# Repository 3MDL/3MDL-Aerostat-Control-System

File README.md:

# Aerostat Control System #
Remote control system of Tetracam RGB+3 Multispectral camera

## Funcions currently implemented ##
- GPS parsing
- Timer based picture taking with settings via EEPROM
- General control over power of attached devices
- RGB+3 diagnostic mode auto-exit

## Functions needed to be implemented ##
- Low battery cuttoff
- Power modes?
- GPS power control on timer like camera

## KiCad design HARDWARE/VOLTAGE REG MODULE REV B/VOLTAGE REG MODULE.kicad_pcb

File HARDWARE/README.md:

# Hardware Docs #

## Load Switch Modules ##
- Utilize the Fairchild FPF2701MX load switch
- Include current shunt resistor and current set resistor

## Voltage Regulator Modules ##
- Stability issues on REV A
- Stability issues on REV B
- Currently using Recom R-78 Module

## Main Board REV C ##
- Redesign that ditches the Pi and instead only uses the ATMega328P
- Uses new Recom R-78 buck regulator module

## Main Board REV D ##
- Fixes numerous pinout issues with REV C
- Passive components moved to bottom side to aid layout
- New connectors are used that utilize side entry to compact the system further

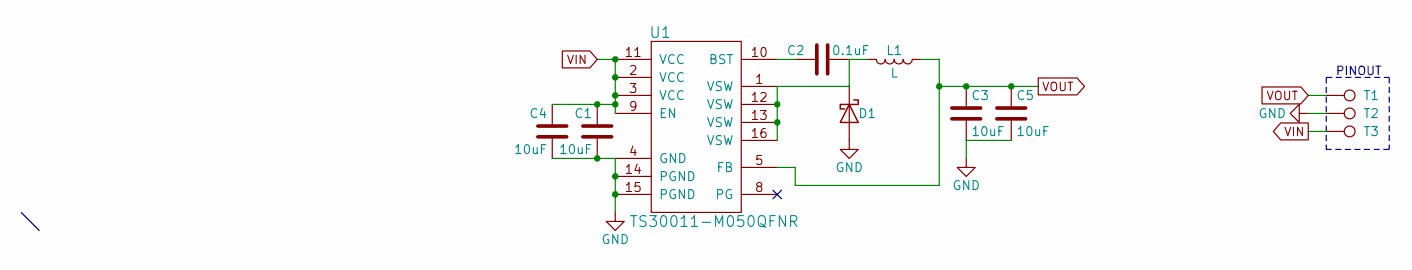
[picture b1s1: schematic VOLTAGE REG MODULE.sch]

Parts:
C1, C3, C4, C5: 10uF; C_0805
C2: 0.1uF; C_0603
D1: D_Schottky; SOD-123
L1: L; C_1210
T1, T2, T3: TEST_1P; CPAD
U1: TS30011-M050QFNR; QFN-16-1EP_3x3mm_Pitch0.5mm

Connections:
GND: C1.2, C3.2, C4.2, C5.2, D1.2 (A), T2.1, U1.4 (GND), U1.14 (PGND), U1.15 (PGND), U1.17
unnamed: C2.1, D1.1 (K), L1.2, U1.1 (VSW), U1.12 (VSW), U1.13 (VSW), U1.16 (VSW)
unnamed: C2.2, U1.10 (BST)
VIN: C1.1, C4.1, T3.1, U1.2 (VCC), U1.3 (VCC), U1.9 (EN), U1.11 (VCC)
VOUT: C3.1, C5.1, L1.1, T1.1, U1.5 (FB)

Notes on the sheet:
PINOUT

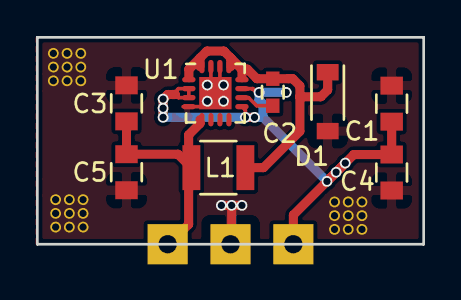
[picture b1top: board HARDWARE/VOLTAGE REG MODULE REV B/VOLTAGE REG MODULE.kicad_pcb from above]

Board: 2 copper layers, 21.5 x 11.5 mm, 11 parts (0 on the bottom side), 5 nets.

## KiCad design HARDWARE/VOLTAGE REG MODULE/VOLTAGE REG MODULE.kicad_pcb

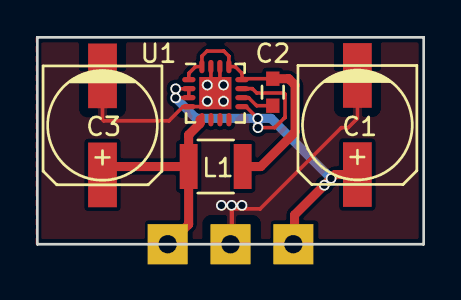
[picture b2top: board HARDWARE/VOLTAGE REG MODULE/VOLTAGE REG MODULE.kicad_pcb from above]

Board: 2 copper layers, 21.5 x 11.5 mm, 8 parts (0 on the bottom side), 5 nets.

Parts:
C1, C3: 10uF; c_elec_6.3x5.8
C2: 0.1uF; C_0603
L1: 470uH; C_1210
T1, T2, T3: TEST_1P; CPAD
U1: TS30011-M050QFNR; QFN-16-1EP_3x3mm_Pitch0.5mm

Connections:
GND: C1.2, C3.2, T3.1, U1.4, U1.14, U1.15, U1.17
unnamed: C2.1, L1.1, U1.1, U1.12, U1.13, U1.16
unnamed: C2.2, U1.10
VIN: C1.1, T1.1, U1.2, U1.3, U1.9, U1.11
VOUT: C3.1, L1.2, T2.1, U1.5

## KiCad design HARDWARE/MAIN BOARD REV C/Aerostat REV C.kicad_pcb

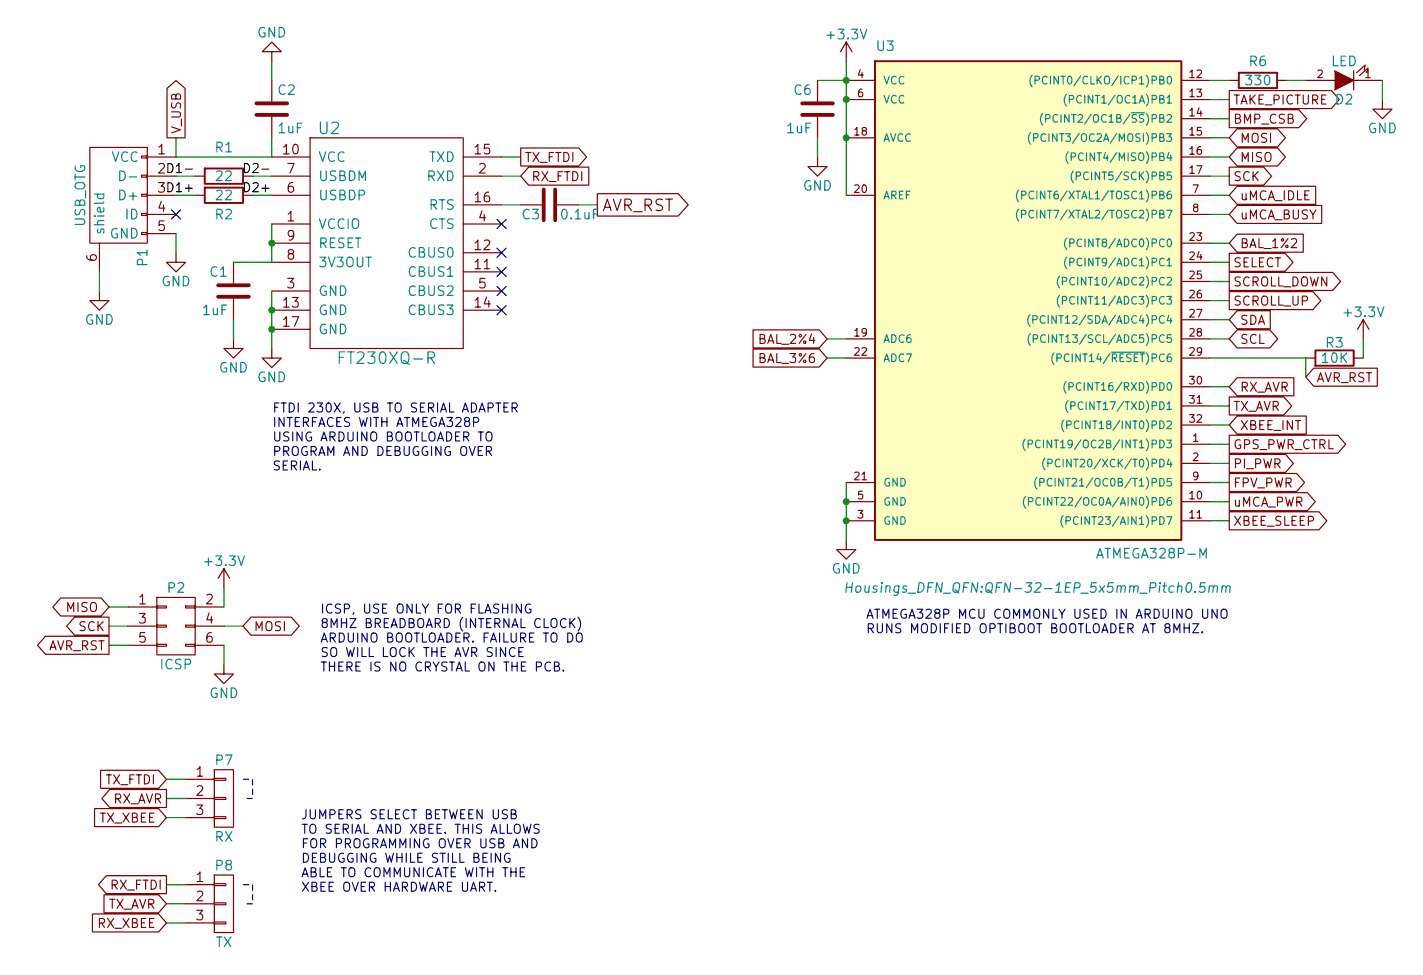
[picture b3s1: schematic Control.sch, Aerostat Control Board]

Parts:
C1, C2, C6: 1uF; C_0603
C3: 0.1uF; C_0603
D2: LED; LED_0603
P1: USB_OTG; UX60-MB-5ST
P2: ICSP; 2.54 ICSP
P7: RX; Pin_Header_Straight_1x03_Pitch2.54mm
P8: TX; Pin_Header_Straight_1x03_Pitch2.54mm
R1, R2: 22; R_0603
R3: 10K; R_0603
R6: 330; R_0603
U2: FT230XQ-R; QFN-16-1EP_4x4mm_Pitch0.65mm
U3: ATMEGA328P-M; QFN-32-1EP_5x5mm_Pitch0.5mm

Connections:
+3V3: C6.1, P2.2, R3.1, U3.4 (VCC), U3.6 (VCC), U3.18 (AVCC), U3.20 (AREF); also elsewhere on the board
/Control/D1+: P1.3 (D+), R2.2
/Control/D1-: P1.2 (D-), R1.2
/Control/D2+: R2.1, U2.6 (USBDP)
/Control/D2-: R1.1, U2.7 (USBDM)
AVR_RST: C3.1, P2.5, R3.2, U3.29 ((PCINT14/~RESET~)PC6)
BAL_1%2: U3.23 ((PCINT8/ADC0)PC0); also elsewhere on the board
BAL_2%4: U3.19 (ADC6); also elsewhere on the board
BAL_3%6: U3.22 (ADC7); also elsewhere on the board
BMP_CSB: U3.14 ((PCINT2/OC1B/~SS~)PB2); also elsewhere on the board
FPV_PWR: U3.9 ((PCINT21/OC0B/T1)PD5); also elsewhere on the board
GND: C1.2, C2.1, C6.2, D2.1 (K), P1.5 (GND), P1.6 (shield), P2.6, U2.3 (GND), U2.13 (GND), U2.17 (GND), U3.3 (GND), U3.5 (GND), U3.21 (GND), U3.33; also elsewhere on the board
GPS_PWR_CTRL: U3.1 ((PCINT19/OC2B/INT1)PD3); also elsewhere on the board
MISO: P2.1, U3.16 ((PCINT4/MISO)PB4); also elsewhere on the board
MOSI: P2.4, U3.15 ((PCINT3/OC2A/MOSI)PB3); also elsewhere on the board
unnamed: C1.1, U2.1 (VCCIO), U2.8 (3V3OUT), U2.9 (RESET)
unnamed: C3.2, U2.16 (RTS)
unnamed: D2.2 (A), R6.1
unnamed: R6.2, U3.12 ((PCINT0/CLKO/ICP1)PB0)
PI_PWR: U3.2 ((PCINT20/XCK/T0)PD4)
RX_AVR: P7.2, U3.30 ((PCINT16/RXD)PD0)
RX_FTDI: P8.1, U2.2 (RXD)
RX_XBEE: P8.3; also elsewhere on the board
SCK: P2.3, U3.17 ((PCINT5/SCK)PB5); also elsewhere on the board
SCL: U3.28 ((PCINT13/SCL/ADC5)PC5); also elsewhere on the board
SCROLL_DOWN: U3.25 ((PCINT10/ADC2)PC2); also elsewhere on the board
SCROLL_UP: U3.26 ((PCINT11/ADC3)PC3); also elsewhere on the board
SDA: U3.27 ((PCINT12/SDA/ADC4)PC4); also elsewhere on the board
SELECT: U3.24 ((PCINT9/ADC1)PC1); also elsewhere on the board
TAKE_PICTURE: U3.13 ((PCINT1/OC1A)PB1); also elsewhere on the board
TX_AVR: P8.2, U3.31 ((PCINT17/TXD)PD1)
TX_FTDI: P7.1, U2.15 (TXD)
TX_XBEE: P7.3; also elsewhere on the board
V_USB: C2.2, P1.1 (VCC), U2.10 (VCC); also elsewhere on the board
XBEE_INT: U3.32 ((PCINT18/INT0)PD2); also elsewhere on the board
XBEE_SLEEP: U3.11 ((PCINT23/AIN1)PD7); also elsewhere on the board
uMCA_BUSY: U3.8 ((PCINT7/XTAL2/TOSC2)PB7); also elsewhere on the board
uMCA_IDLE: U3.7 ((PCINT6/XTAL1/TOSC1)PB6); also elsewhere on the board
uMCA_PWR: U3.10 ((PCINT22/OC0A/AIN0)PD6); also elsewhere on the board

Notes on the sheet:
JUMPERS SELECT BETWEEN USB TO SERIAL AND XBEE. THIS ALLOWS FOR PROGRAMMING OVER USB AND DEBUGGING WHILE STILL BEING ABLE TO COMMUNICATE WITH THE XBEE OVER HARDWARE UART.
ICSP, USE ONLY FOR FLASHING 8MHZ BREADBOARD (INTERNAL CLOCK) ARDUINO BOOTLOADER. FAILURE TO DO SO WILL LOCK THE AVR SINCE THERE IS NO CRYSTAL ON THE PCB.
FTDI 230X, USB TO SERIAL ADAPTER INTERFACES WITH ATMEGA328P USING ARDUINO BOOTLOADER TO PROGRAM AND DEBUGGING OVER SERIAL.
ATMEGA328P MCU COMMONLY USED IN ARDUINO UNO RUNS MODIFIED OPTIBOOT BOOTLOADER AT 8MHZ.

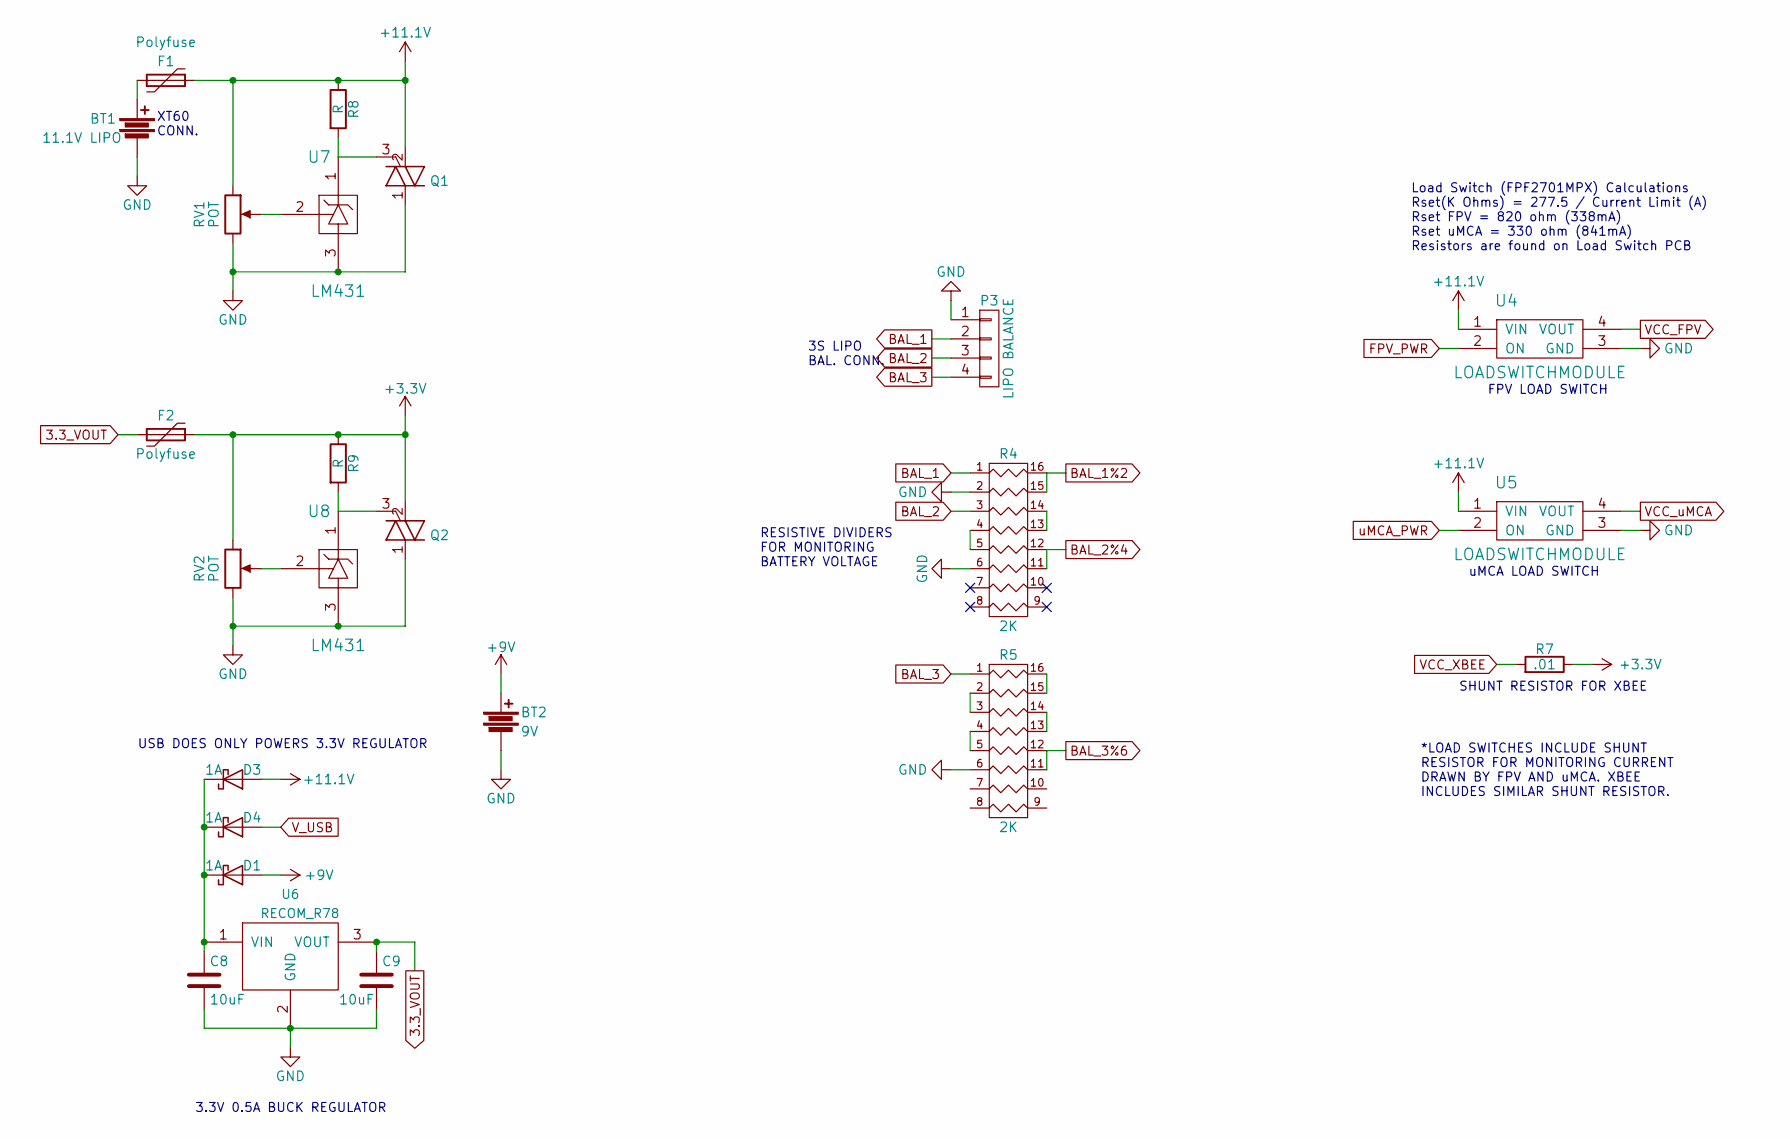
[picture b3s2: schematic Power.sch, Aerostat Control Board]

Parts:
BT1: 11.1V LIPO; XT60
BT2: 9V; TE1X2
C8, C9: 10uF; C_0603
D1, D3, D4: 1A; D_SOD-123
F1, F2: Polyfuse; C_1210
P3: LIPO BALANCE; JST_B4B-XH-A(LF)(SN)
Q1, Q2: Q_TRIAC_AAG; Pin_Header_Straight_1x03_Pitch2.54mm
R4, R5: 2K; R_Array_Convex_8x0602
R7: .01; R_0805
R8, R9: R; R_0603
RV1, RV2: POT; Potentiometer_Trimmer-EVM3E
U4, U5: LOADSWITCHMODULE; LOAD SWITCH MODULE
U6: RECOM_R78; R-78E
U7, U8: LM431; SOT-323_SC-70

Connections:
3.3_VOUT: C9.1, F2.2, U6.3 (VOUT)
+3V3: F2.1, Q2.2 (A2), R7.1, R9.1, RV2.1; also elsewhere on the board
+9V: BT2.1, D1.2 (A)
+12C: D3.2 (A), F1.1, Q1.2 (A2), R8.1, RV1.1, U4.1 (VIN), U5.1 (VIN)
BAL_1: P3.2, R4.1
BAL_1%2: R4.15 (R2), R4.16 (R1); also elsewhere on the board
BAL_2: P3.3, R4.3
BAL_2%4: R4.11 (R6), R4.12 (R5); also elsewhere on the board
BAL_3: P3.4, R5.1
BAL_3%6: R5.11 (R6), R5.12 (R5); also elsewhere on the board
FPV_PWR: U4.2 (ON); also elsewhere on the board
GND: BT1.2, BT2.2, C8.2, C9.2, P3.1, Q1.1 (A1), Q2.1 (A1), R4.2, R4.6, R5.6, RV1.3, RV2.3, U4.3 (GND), U5.3 (GND), U6.2 (GND), U7.3, U8.3; also elsewhere on the board
unnamed: BT1.1, F1.2
unnamed: C8.1, D1.1 (K), D3.1 (K), D4.1 (K), U6.1 (VIN)
unnamed: Q1.3 (G), R8.2, U7.1
unnamed: Q2.3 (G), R9.2, U8.1
unnamed: R4.4, R4.5
unnamed: R4.13 (R4), R4.14 (R3)
unnamed: R5.2, R5.3
unnamed: R5.4, R5.5
unnamed: R5.13 (R4), R5.14 (R3)
unnamed: R5.15 (R2), R5.16 (R1)
unnamed: RV1.2, U7.2
unnamed: RV2.2, U8.2
VCC_FPV: U4.4 (VOUT); also elsewhere on the board
VCC_XBEE: R7.2; also elsewhere on the board
VCC_uMCA: U5.4 (VOUT); also elsewhere on the board
V_USB: D4.2 (A); also elsewhere on the board
uMCA_PWR: U5.2 (ON); also elsewhere on the board

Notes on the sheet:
XT60 CONN.
3S LIPO BAL. CONN.
RESISTIVE DIVIDERS FOR MONITORING BATTERY VOLTAGE
FPV LOAD SWITCH
uMCA LOAD SWITCH
SHUNT RESISTOR FOR XBEE
*LOAD SWITCHES INCLUDE SHUNT RESISTOR FOR MONITORING CURRENT DRAWN BY FPV AND uMCA. XBEE INCLUDES SIMILAR SHUNT RESISTOR.
Load Switch (FPF2701MPX) Calculations Rset(K Ohms) = 277.5 / Current Limit (A) Rset FPV = 820 ohm (338mA) Rset uMCA = 330 ohm (841mA) Resistors are found on Load Switch PCB
3.3V 0.5A BUCK REGULATOR
USB DOES ONLY POWERS 3.3V REGULATOR

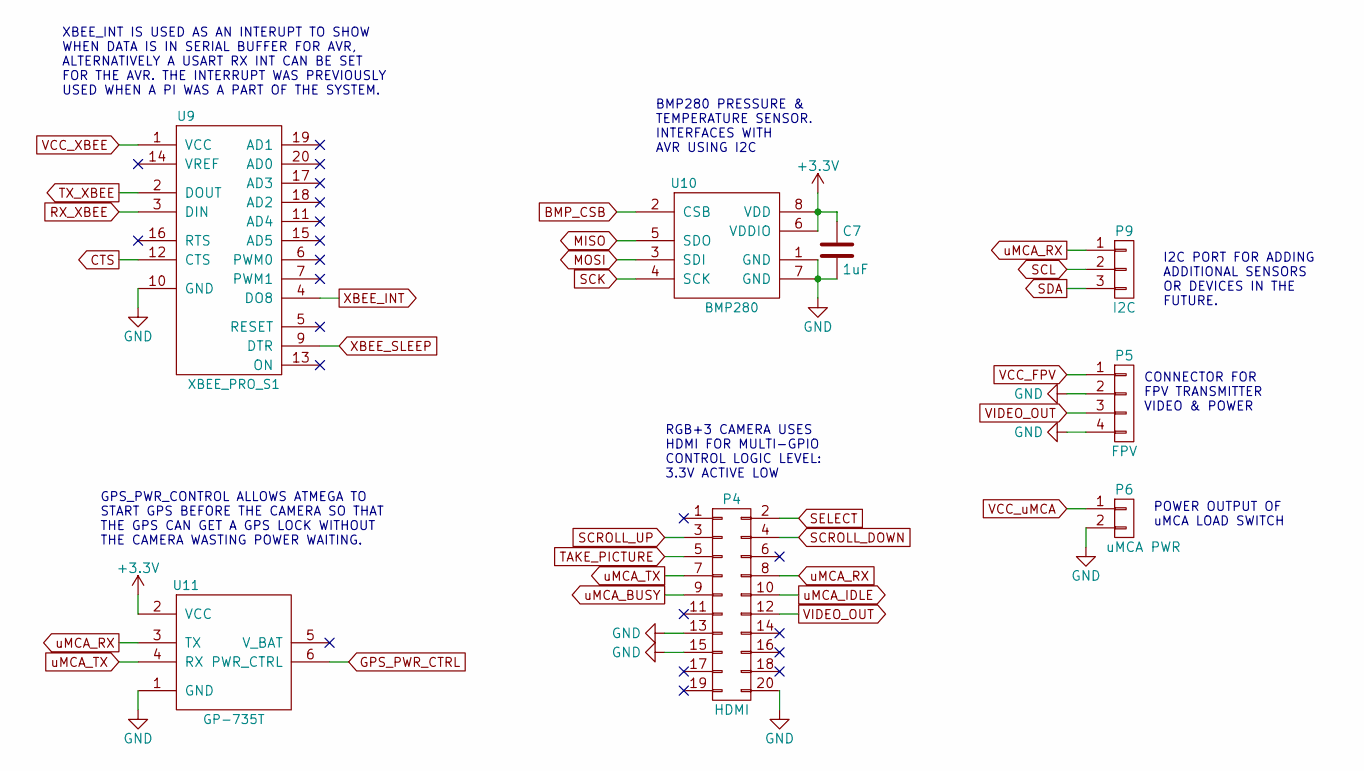
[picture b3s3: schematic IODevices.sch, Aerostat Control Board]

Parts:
C7: 1uF; C_0603
P4: HDMI; 10029449-111RLF
P5: FPV; TE1X4
P6: uMCA PWR; TE1X2
P9: I2C; Pin_Header_Straight_1x03_Pitch2.54mm
U9: XBEE_PRO_S1; DIP-20
U10: BMP280; LGA-8
U11: GP-735T

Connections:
+3V3: C7.1, U10.6 (VDDIO), U10.8 (VDD), U11.2 (VCC); also elsewhere on the board
BMP_CSB: U10.2 (CSB); also elsewhere on the board
CTS: U9.12 (CTS)
GND: C7.2, P4.13, P4.15, P4.20, P5.2, P5.4, P6.2, U9.10 (GND), U10.1 (GND), U10.7 (GND), U11.1 (GND), U11.7; also elsewhere on the board
GPS_PWR_CTRL: U11.6 (PWR_CTRL); also elsewhere on the board
MISO: U10.5 (SDO); also elsewhere on the board
MOSI: U10.3 (SDI); also elsewhere on the board
RX_XBEE: U9.3 (DIN); also elsewhere on the board
SCK: U10.4 (SCK); also elsewhere on the board
SCL: P9.2; also elsewhere on the board
SCROLL_DOWN: P4.4; also elsewhere on the board
SCROLL_UP: P4.3; also elsewhere on the board
SDA: P9.3; also elsewhere on the board
SELECT: P4.2; also elsewhere on the board
TAKE_PICTURE: P4.5; also elsewhere on the board
TX_XBEE: U9.2 (DOUT); also elsewhere on the board
VCC_FPV: P5.1; also elsewhere on the board
VCC_XBEE: U9.1 (VCC); also elsewhere on the board
VCC_uMCA: P6.1; also elsewhere on the board
VIDEO_OUT: P4.12, P5.3
XBEE_INT: U9.4 (DO8); also elsewhere on the board
XBEE_SLEEP: U9.9 (DTR); also elsewhere on the board
uMCA_BUSY: P4.9; also elsewhere on the board
uMCA_IDLE: P4.10; also elsewhere on the board
uMCA_RX: P4.8, P9.1, U11.3 (TX)
uMCA_TX: P4.7, U11.4 (RX)

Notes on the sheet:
GPS_PWR_CONTROL ALLOWS ATMEGA TO START GPS BEFORE THE CAMERA SO THAT THE GPS CAN GET A GPS LOCK WITHOUT THE CAMERA WASTING POWER WAITING.
XBEE_INT IS USED AS AN INTERUPT TO SHOW WHEN DATA IS IN SERIAL BUFFER FOR AVR, ALTERNATIVELY A USART RX INT CAN BE SET FOR THE AVR. THE INTERRUPT WAS PREVIOUSLY USED WHEN A PI WAS A PART OF THE SYSTEM.
POWER OUTPUT OF uMCA LOAD SWITCH
CONNECTOR FOR FPV TRANSMITTER VIDEO & POWER
RGB+3 CAMERA USES HDMI FOR MULTI-GPIO CONTROL LOGIC LEVEL: 3.3V ACTIVE LOW
BMP280 PRESSURE & TEMPERATURE SENSOR. INTERFACES WITH AVR USING I2C
I2C PORT FOR ADDING ADDITIONAL SENSORS OR DEVICES IN THE FUTURE.

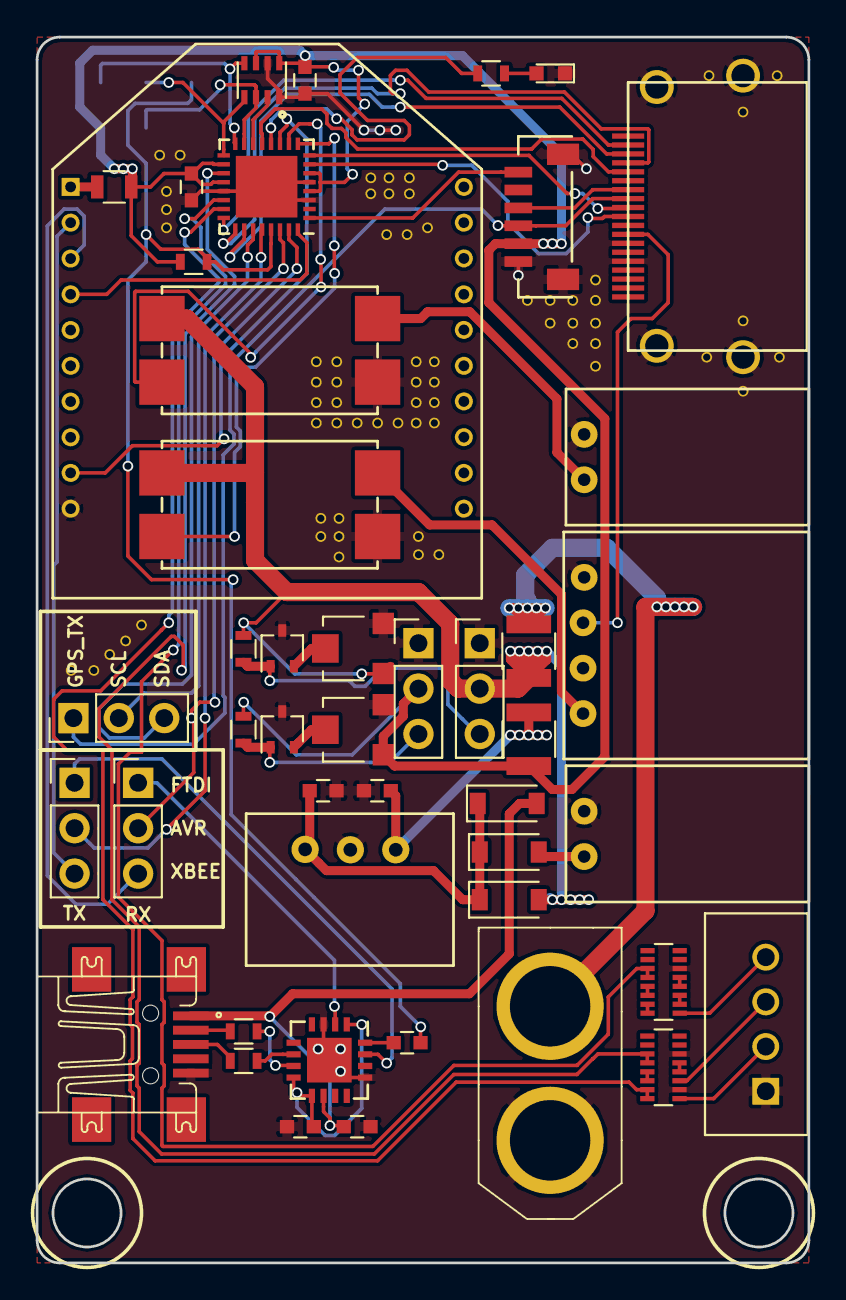
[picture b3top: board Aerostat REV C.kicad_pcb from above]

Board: 2 copper layers, 43.2 x 68.6 mm, 47 parts (1 on the bottom side), 62 nets.

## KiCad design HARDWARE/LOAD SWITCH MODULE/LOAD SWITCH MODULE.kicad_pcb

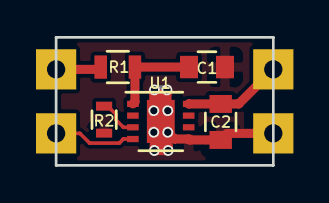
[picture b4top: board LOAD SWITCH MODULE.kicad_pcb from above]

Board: 2 copper layers, 12.1 x 7.1 mm, 9 parts (0 on the bottom side), 6 nets.

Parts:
C1, C2: 10uF; C_0805
R1: 0.01; R_0805
R2: R; R_0603
T1, T2, T3, T4: TEST_1P; CPAD
U1: FPF2701MPX; DFN-8-1EP_3x3mm_Pitch0.65mm

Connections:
GND: C1.2, C2.1, R2.2, T4.1, U1.5, U1.9
unnamed: C1.1, R1.1, U1.1
unnamed: R2.1, U1.3
ON: T3.1, U1.4
VIN: R1.2, T1.1
VOUT: C2.2, T2.1, U1.8

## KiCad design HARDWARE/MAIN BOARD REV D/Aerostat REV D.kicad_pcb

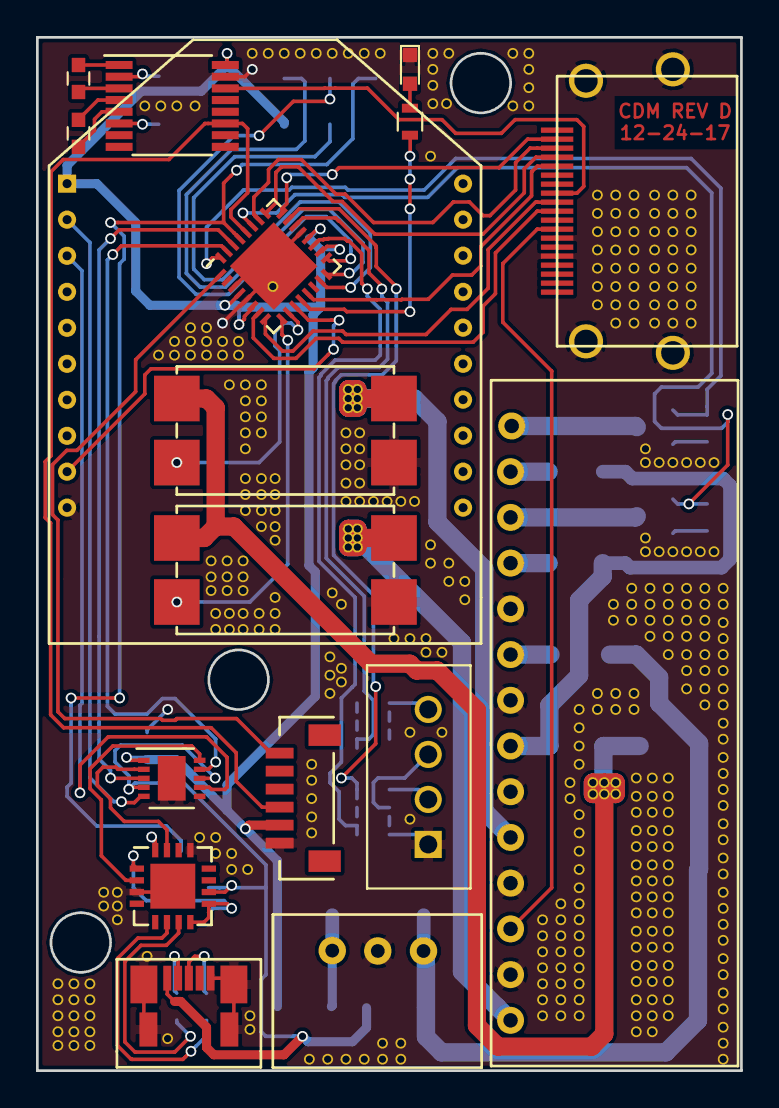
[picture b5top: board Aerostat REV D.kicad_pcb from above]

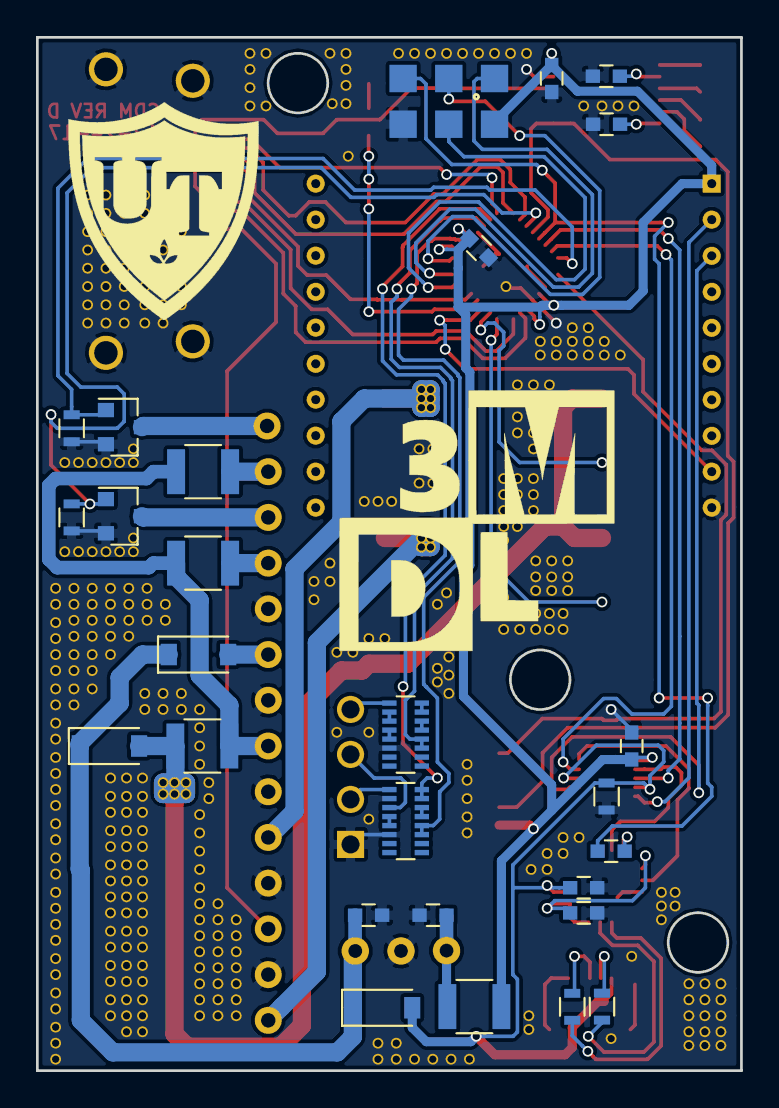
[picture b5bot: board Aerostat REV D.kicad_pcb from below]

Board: 2 copper layers, 39.1 x 57.4 mm, 44 parts (27 on the bottom side), 65 nets.

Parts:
C1, C2, C3, C5, C9, C10: 1uF; C_0603
C4: 0.1uF; C_0603
C6, C7: 10uF; C_0603
C8, C11, C12: .1uF; C_0603
D1: LED; LED_0603
D2, D3, D4: 1A; D_SOD-123
F1: Polyfuse; C_1210
F2, F3, F4: 1A; C_1210
P1: USB_OTG; 0473461001_GLUE
P2: ICSP; 2.54 ICSP
P3: LIPO BALANCE; JST_B4B-XH-A(LF)(SN)
P4: HDMI; 10029449-111RLF
P5: CONN_01X14; TE1X14
Q2, Q3: Q_NMOS_GSD; SOT-23
R1, R10, R11: 10K; R_0603
R2, R3: 22; R_0603
R4: 330; R_0603
R7, R8: 2K; R_Array_Convex_8x0602
U1: NLAS4684; DFN-10-1EP_3x3mm_Pitch0.5mm
U2: FT230XQ-R; QFN-16-1EP_4x4mm_Pitch0.65mm
U3: ATMEGA328P-M; QFN-32-1EP_5x5mm_Pitch0.5mm
U4: RECOM_R78; R-78E
U6, U7: LOADSWITCHMODULE; LOAD SWITCH MODULE
U8: XBEE_PRO_S1; DIP-20
U9: GP-735T
U10: MAX3232; TSSOP-16_4.4x5mm_Pitch0.65mm

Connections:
11.1V_IN: F1.2, F3.2, F4.2, P5.7
+3V3: C1.2, C5.1, C10.2, F2.2, P2.2, U1.1, U3.4, U3.6, U3.18, U3.20, U8.1, U9.2, U10.16
+9V: D4.2, P5.9
+12C: D2.2, F1.1, U6.1, U7.1
/Control/D1+: P1.3, R3.2
/Control/D1-: P1.2, R2.2
/Control/D2+: R3.1, U2.6
/Control/D2-: R2.1, U2.7
AVR_RST: C4.1, P2.5, U3.29
BAL_1: P3.2, R7.1
BAL_1%2: R7.15, R7.16, U3.23
BAL_2: P3.3, R7.3
BAL_2%4: R7.11, R7.12, U3.19
BAL_3: P3.4, R8.1
BAL_3%6: R8.11, R8.12, U3.22
FPV_PWR: U3.9, U6.2
GND: C1.1, C2.2, C3.1, C5.2, C6.2, C7.2, C10.1, C11.1, C12.1, D1.1, P1.5, P2.6, P3.1, P4.13, P4.15, P4.20, P5.2, P5.4, P5.6, P5.8, P5.10, Q2.2, Q3.2, R1.2, R7.2, R7.6, R8.6, R10.2, R11.2, U1.6, U2.3, U2.13, U2.17, U3.3, U3.5, U3.21, U4.2, U6.3, U7.3, U8.10, U9.1, U10.15
GPS_PWR_CTRL: U3.1, U9.6
GPS_TX: U3.28, U9.3, U10.11
MISO: P2.1, U3.16
MOSFET_A: Q2.1, R10.1, U3.27
MOSFET_A_OUT: P5.12, Q2.3
MOSFET_B: Q3.1, R11.1, U3.32
MOSFET_B_OUT: P5.14, Q3.3
MOSI: P2.4, U3.15
unnamed: C2.1, U2.1, U2.8, U2.9
unnamed: C4.2, U2.16
unnamed: C6.1, D2.1, D3.1, D4.1, U4.1
unnamed: C7.1, F2.1, U4.3
unnamed: C8.1, U10.3
unnamed: C8.2, U10.1
unnamed: C9.1, U10.5
unnamed: C9.2, U10.4
unnamed: C11.2, U10.2
unnamed: C12.2, U10.6
unnamed: D1.2, R4.1
unnamed: F3.1, P5.11
unnamed: F4.1, P5.13
unnamed: R4.2, U3.12
unnamed: R7.4, R7.5
unnamed: R7.13, R7.14
unnamed: R8.2, R8.3
unnamed: R8.4, R8.5
unnamed: R8.13, R8.14
unnamed: R8.15, R8.16
RX_AVR: U1.3, U3.30
RX_FTDI: U1.10, U2.2
RX_XBEE: U1.7, U8.3
SCK: P2.3, U3.17
SCROLL_DOWN: P4.4, U3.25
SCROLL_UP: P4.3, U3.26
SELECT: P4.2, U3.24
TAKE_PICTURE: P4.5, U3.13
TX_AVR: U1.9, U3.31
TX_FTDI: U1.2, U2.15
TX_XBEE: U1.5, U8.2
VCC_FPV: P5.1, U6.4
VCC_uMCA: P5.5, U7.4
VIDEO_OUT: P4.12, P5.3
V_USB: C3.2, D3.2, P1.1, R1.1, U1.4, U1.8, U2.10
XBEE_SLEEP: U3.11, U8.9
uMCA_BUSY: P4.9, U3.8
uMCA_IDLE: P4.10, U3.7
uMCA_PWR: U3.10, U7.2
uMCA_RX: P4.8, U10.14

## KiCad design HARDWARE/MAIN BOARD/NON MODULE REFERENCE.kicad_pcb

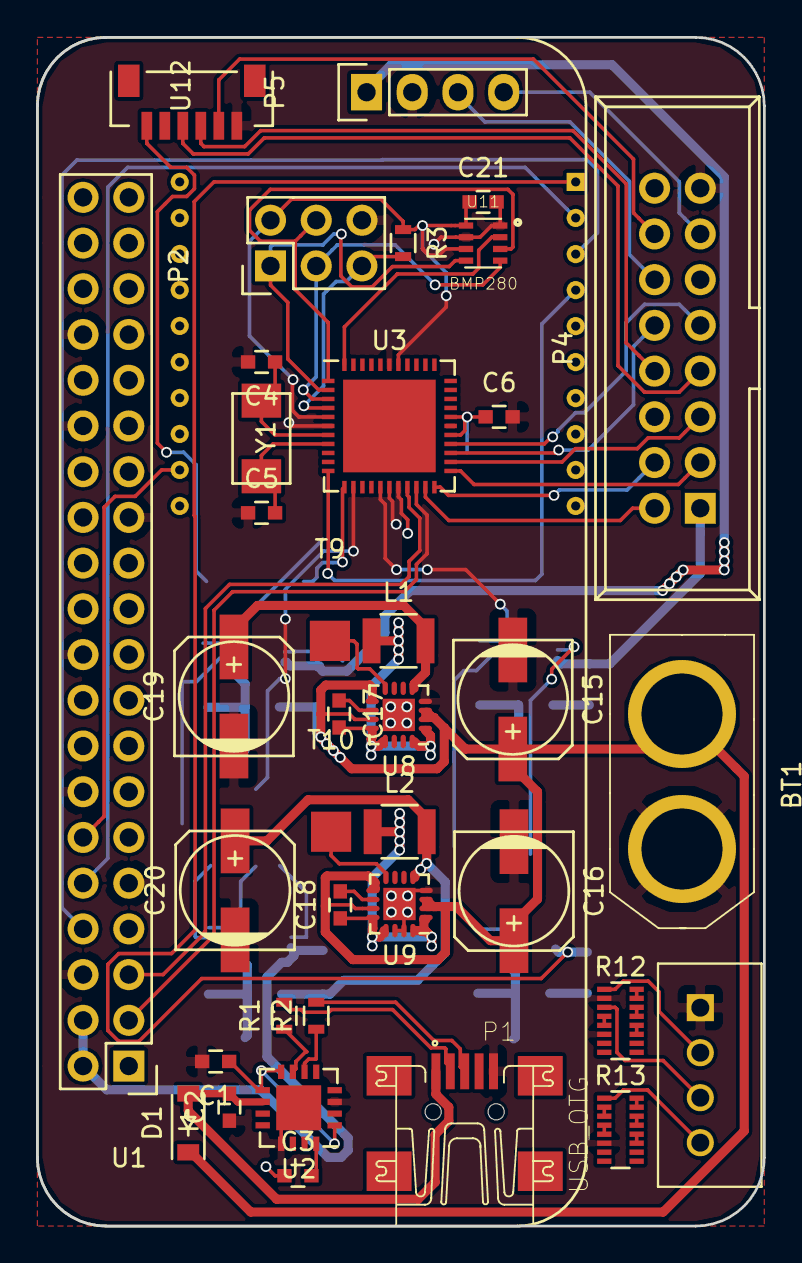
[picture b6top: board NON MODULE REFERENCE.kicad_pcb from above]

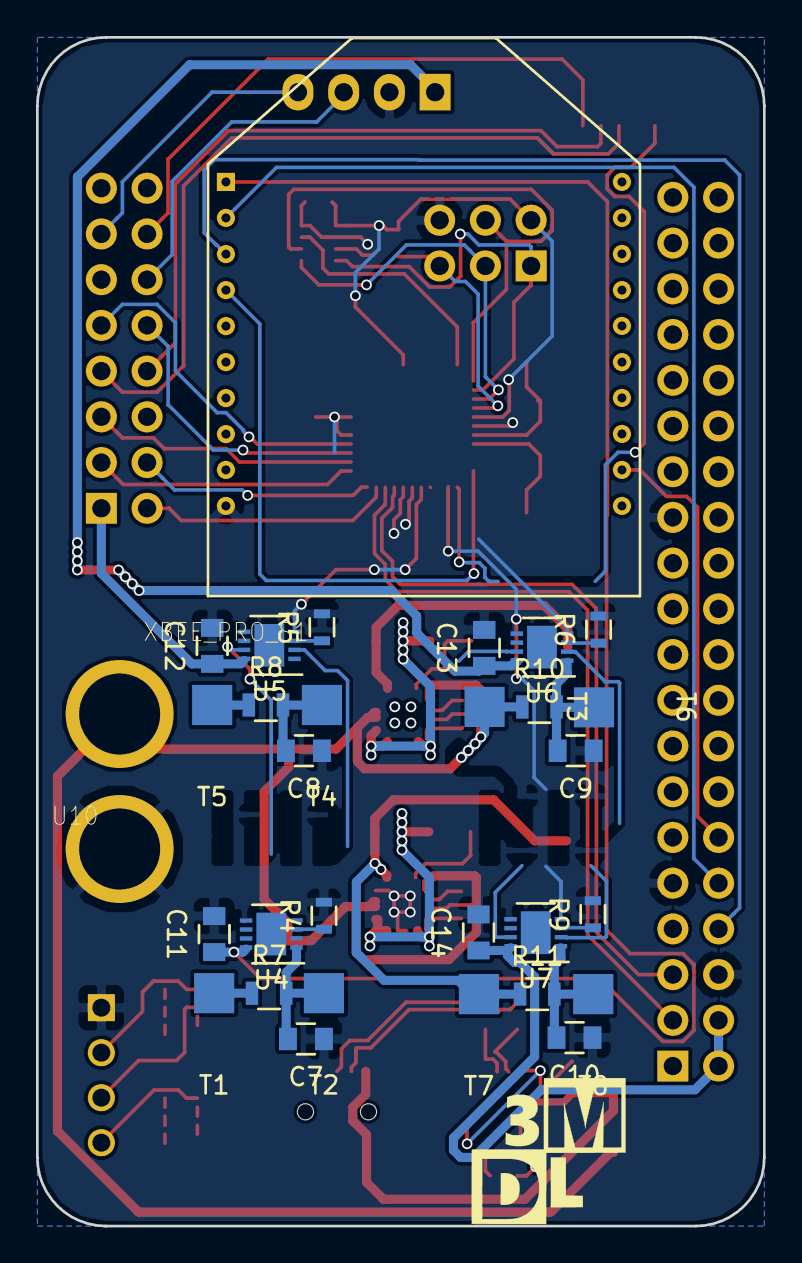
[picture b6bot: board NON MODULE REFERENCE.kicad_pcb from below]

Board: 2 copper layers, 40.4 x 66.0 mm, 66 parts (29 on the bottom side), 74 nets.

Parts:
BT1: 11.1V LIPO; XT60
C1, C2, C6, C21: 1uF; C_0603
C3, C17, C18: 0.1uF; C_0603
C4, C5: 22pF; C_0603
C7, C8, C9, C10, C11, C12, C13, C14: 10uF; C_0805
C15, C16, C19, C20: 10uF; c_elec_6.3x5.8
D1: 1A; SOD-123
L1, L2: 470uH; C_1210
P1: USB_OTG; UX60-MB-5ST
P2: ICSP; Pin_Header_Straight_2x03
P3: LIPO BALANCE; JST_B4B-XH-A(LF)(SN)
P4: Multi GPIO; IDC_Header_Straight_16pins
P5: FPV; Pin_Header_Straight_1x04
R1, R2: 22; R_0603
R3: 10K; R_0603
R4, R9: 680; R_0603
R5: 330; R_0603
R6: 820; R_0603
R7, R8, R10, R11: 0.1; R_0805
R12, R13: R_PACK8; R_Array_Convex_8x0602
T1, T2, T3, T4, T5, T6, T7, T8, T9, T10: CONN_01X01; TEST_POINT
U1: Pi_Zero_W
U2: FT230XQ-R; QFN-16-1EP_4x4mm_Pitch0.65mm
U3: ATMEGA644A-M; QFN-44-1EP_7x7mm_Pitch0.5mm
U4, U5, U6, U7: FPF2701MPX; DFN-8-1EP_3x3mm_Pitch0.5mm
U8: TS30011-M033QFNR; QFN-16-1EP_3x3mm_Pitch0.5mm
U9: TS30011-M050QFNR; QFN-16-1EP_3x3mm_Pitch0.5mm
U10: XBEE_PRO_S1; DIP-20
U11: BMP280; LGA-8
U12: GP-735T
Y1: 8MHz; ABM3

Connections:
+3V3: C6.1, C19.1, C21.1, L1.2, P2.2, R3.1, R7.1, T1.1, U3.5, U3.17, U3.27, U3.29, U3.38, U8.5, U11.6, U11.8
+5V: C20.1, L2.2, R11.1, T7.1, U9.5
+12C: BT1.1, C15.1, C16.1, D1.1, R8.1, R10.1, T3.1, T5.1, U8.2, U8.3, U8.9, U8.11, U9.2, U9.3, U9.9, U9.11
/Control/D1+: P1.3, R2.2
/Control/D1-: P1.2, R1.2
/Control/D2+: R2.1, U2.6
/Control/D2-: R1.1, U2.7
AVR_RST: C3.1, P2.5, R3.2, U3.4
BAL_1: P3.2, R12.1
BAL_1%2: R12.15, R12.16
BAL_2: P3.3, R12.3
BAL_2%4: R12.11, R12.12
BAL_3: P3.4, R13.1
BAL_3%6: R13.11, R13.12
BMP_CSB: U3.44, U11.2
CTS: U1.26, U10.12
FLAGB_2: U3.41, U4.7
GND: BT1.2, C1.2, C2.1, C4.2, C5.1, C6.2, C7.1, C8.1, C9.1, C10.1, C11.2, C12.2, C13.2, C14.2, C15.2, C16.2, C19.2, C20.2, C21.2, P1.5, P2.6, P3.1, P4.15, P5.2, R4.2, R5.2, R6.2, R9.2, R12.2, R12.6, R13.6, U1.5, U1.13, U1.23, U1.27, U1.30, U1.35, U1.37, U2.3, U2.13, U2.17, U3.6, U3.18, U3.28, U3.39, U4.5, U4.9, U5.5, U5.9, U6.5, U6.9, U7.5, U7.9, U8.4, U8.14, U8.15, U9.4, U9.14, U9.15, U9.17, U10.10, U11.1, U11.7, U12.1
GPS_PWR_CTRL: U3.12, U12.6
MISO: P2.1, U3.2, U11.5
MOSI: P2.4, U3.1, U11.3
unnamed: C1.1, U2.1, U2.8, U2.9
unnamed: C2.2, D1.2, P1.1, U2.10
unnamed: C3.2, U2.16
unnamed: C4.1, U3.7, Y1.1
unnamed: C5.2, U3.8, Y1.2
unnamed: C7.2, R7.2, T2.1, U4.1
unnamed: C8.2, R8.2, T4.1, U5.1
unnamed: C9.2, R10.2, T6.1, U6.1
unnamed: C10.2, R11.2, T8.1, U7.1
unnamed: C17.1, U8.10
unnamed: C17.2, L1.1, U8.1, U8.12, U8.13, U8.16
unnamed: C18.1, L2.1, U9.1, U9.12, U9.13, U9.16
unnamed: C18.2, U9.10
unnamed: R4.1, U4.3
unnamed: R5.1, U5.3
unnamed: R6.1, U6.3
unnamed: R9.1, U7.3
unnamed: R12.4, R12.5
unnamed: R12.13, R12.14
unnamed: R13.2, R13.3
unnamed: R13.4, R13.5
unnamed: R13.13, R13.14
unnamed: R13.15, R13.16
unnamed: T9.1, U8.8
unnamed: T10.1, U9.8
ON_1: U3.13, U7.4
ON_2: U3.14, U4.4
ON_3: U3.15, U6.4
ON_4: U3.16, U5.4
PGOOD_2: U3.32, U4.2
RX_AVR: U2.15, U3.9
RX_PI: U1.25, U10.2
SCK: P2.3, U3.3, U11.4
SCL: U1.3, U3.19
SCROLL_DOWN: P4.4, U3.22
SCROLL_UP: P4.3, U3.23
SDA: U1.2, U3.20
SELECT: P4.2, U3.21
TAKE_PICTURE: P4.5, U3.24
TX_AVR: U2.2, U3.10
TX_PI: U1.24, U10.3
VCC_FPV: C13.1, P5.1, U6.8
VCC_GPS: P4.14, U12.2
VCC_PI: C14.1, U1.21, U1.22, U7.8
VCC_XBEE: C11.1, U4.8, U10.1
VCC_uMCA: C12.1, P4.1, U5.8
VIDEO_GND: P4.13, P5.4
VIDEO_OUT: P4.12, P5.3
XBEE_INT: U3.11, U10.4
uMCA_BUSY: P4.9, U3.26
uMCA_IDLE: P4.10, U3.25
uMCA_RX: P4.8, U12.3
uMCA_TX: P4.7, U12.4

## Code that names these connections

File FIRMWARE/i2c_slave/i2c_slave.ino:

/*#include <Wire.h>
#include <SPI.h>

#include <Adafruit_Sensor.h>
#include <Adafruit_BMP280.h>
//Arduino Pro Mini Pin Map
#define PD1 1
#define PD0 0
#define PD2 2
#define PD3 3
#define PD4 4
#define PD5 5
#define PD6 6
#define PD7 7
#define PB0 8
#define PB1 9
#define PC3 17
#define PC2 16
#define PC1 15
#define PC0 14
#define PB5 13
#define PB4 12
#define PB3 11
#define PB2 10
#define PC4 A4
#define PC5 A5
//A7 and A6 already used in Port Names directly

//AVR Port Names
#define TAKE_PICTURE PB1
#define BMP_CSB 10 //PB2
#define uMCA_IDLE PB6
#define uMCA_BUSY PB7
#define SELECT PC1
#define SCROLL_DOWN PC2
#define SCROLL_UP PC3
#define XBEE_INT PD2
#define GPS_PWR_CTRL PD3
#define PI_PWR PD4
#define FPV_PWR PD5
#define uMCA_PWR 6
#define XBEE_SLEEP PD7
#define BAL_1 PC0
#define BAL_2 A6
#define BAL_3 A7
#define LED PB0

Adafruit_BMP280 bmp(BMP_CSB);

void setup() {
  //set inputs and outputs
  pinMode(TAKE_PICTURE, OUTPUT);
  pinMode(BMP_CSB, OUTPUT);
  pinMode(uMCA_IDLE, INPUT);
  pinMode(uMCA_BUSY, INPUT);
  pinMode(BAL_1, INPUT);
  pinMode(BAL_2, INPUT);
  pinMode(BAL_3, INPUT);
  pinMode(SELECT, OUTPUT);
  pinMode(SCROLL_DOWN, OUTPUT);
  pinMode(SCROLL_UP, OUTPUT);
  pinMode(XBEE_INT, INPUT);
  pinMode(GPS_PWR_CTRL, OUTPUT);
  pinMode(PI_PWR, OUTPUT);
  pinMode(FPV_PWR, OUTPUT);
  pinMode(uMCA_PWR, OUTPUT);
  pinMode(XBEE_SLEEP, OUTPUT);
  pinMode(LED, OUTPUT);
  //turn all load switches off and xbee off
  digitalWrite(PI_PWR, LOW);
  digitalWrite(FPV_PWR, LOW);
  digitalWrite(uMCA_PWR, LOW);
  digitalWrite(XBEE_SLEEP, HIGH);
  //start i2c interface
  Wire.begin(0X60);
  Wire.onRequest(transmit);
  Wire.onReceive(receive);
  //start serial interface
  Serial.begin(9600);
  //start spi interface
  /*if (!bmp.begin()) {
    Serial.println(F("Could not find a valid BMP280 sensor, check wiring!"));
    while (1);
  }*/
}
/*
int c[] = { -1, -1, -1}; //command, parameter 1, parameter 2

void loop() {
    digitalWrite(uMCA_PWR, LOW); //turn uMCA on
  if (Serial.available()) {
    char c = Serial.read();
    if (c == 'm') { //menu
      Serial.println("menu");
      digitalWrite(SELECT, LOW);
      delay(100);
      digitalWrite(SELECT, HIGH);
    } else if (c == 'u') { //up
      Serial.println("up");
      digitalWrite(SCROLL_UP, LOW);
      delay(100);
      digitalWrite(SCROLL_UP, HIGH);
    } else if (c == 'd') { //down
      Serial.println("down");
      digitalWrite(SCROLL_DOWN, LOW);
      delay(100);
      digitalWrite(A2, HIGH);
    } else if (c == 'p') { //picture
      Serial.println("picture");
      digitalWrite(TAKE_PICTURE, LOW);
      delay(100);
      digitalWrite(TAKE_PICTURE, HIGH);
    }
  }
  delay(1000);
  int alt = bmp.readAltitude(1013.25);
  Serial.println(alt);
}

int output; //holds i2c transmit message

void receive() {
  digitalWrite(LED, !digitalRead(LED));
  int data = Wire.read();
  if (c[0] == -1) {
    c[0] = data;
  } else if (c[1] == -1) {
    c[1] = data;
  } else if (c[2] == -1) {
    c[2] = data;
  }
  Serial.println(c[0]);
  Serial.println(c[1]);
  Serial.println(c[2]);
  switch (c[0]) {
    case 1: //readAlt
      output = bmp.readAltitude(1013.25);
      c[0] = -1; c[1] = -1; c[2] = -1;
      break;
    case 101: //readCell
      output = analogRead("CELL_" + c[1]);
      c[0] = -1; c[1] = -1; c[2] = -1;
      break;
    case 102: //takePic
      digitalWrite(TAKE_PICTURE, LOW);
      delay(100);
      digitalWrite(TAKE_PICTURE, HIGH);
      c[0] = -1; c[1] = -1; c[2] = -1;
      break;
    case 201: //setGPIO
      if (c[1] != 999 && c[2] != 999) {
        digitalWrite(c[1], c[2]);
        c[0] = -1; c[1] = -1; c[2] = -1;
      }
      break;
  }
}
void transmit() {
  Wire.write(output);
}
*/
#include "TinyGPS++.h"

// A sample NMEA stream.
const char *gpsStream =
  "$GPRMC,045103.000,A,3014.1984,N,09749.2872,W,0.67,161.46,030913,,,A*7C\r\n"
  "$GPGGA,045104.000,3014.1985,N,09749.2873,W,1,09,1.2,211.6,M,-22.5,M,,0000*62\r\n"
  "$GPRMC,045200.000,A,3014.3820,N,09748.9514,W,36.88,65.02,030913,,,A*77\r\n"
  "$GPGGA,045201.000,3014.3864,N,09748.9411,W,1,10,1.2,200.8,M,-22.5,M,,0000*6C\r\n"
  "$GPRMC,045251.000,A,3014.4275,N,09749.0626,W,0.51,217.94,030913,,,A*7D\r\n"
  "$GPGGA,045252.000,3014.4273,N,09749.0628,W,1,09,1.3,206.9,M,-22.5,M,,0000*6F\r\n";

// The TinyGPS++ object
TinyGPSPlus gps;

void setup()
{
  Serial.begin(115200);

  Serial.println(F("BasicExample.ino"));
  Serial.println(F("Basic demonstration of TinyGPS++ (no device needed)"));
  Serial.print(F("Testing TinyGPS++ library v. ")); Serial.println(TinyGPSPlus::libraryVersion());
  Serial.println(F("by Mikal Hart"));
  Serial.println();

  while (*gpsStream)
    if (gps.encode(*gpsStream++))
      displayInfo();

  Serial.println();
  Serial.println(F("Done."));
}

void loop()
{
}

void displayInfo()
{
  Serial.print(F("Location: ")); 
  if (gps.location.isValid())
  {
    Serial.print(gps.location.lat(), 6);
    Serial.print(F(","));
    Serial.print(gps.location.lng(), 6);
  }
  else
  {
    Serial.print(F("INVALID"));
  }

  Serial.print(F("  Date/Time: "));
  if (gps.date.isValid())
  {
    Serial.print(gps.date.month());
    Serial.print(F("/"));
    Serial.print(gps.date.day());
    Serial.print(F("/"));
    Serial.print(gps.date.year());
  }
  else
  {
    Serial.print(F("INVALID"));
  }

  Serial.print(F(" "));
  if (gps.time.isValid())
  {
    if (gps.time.hour() < 10) Serial.print(F("0"));
    Serial.print(gps.time.hour());
    Serial.print(F(":"));
    if (gps.time.minute() < 10) Serial.print(F("0"));
    Serial.print(gps.time.minute());
    Serial.print(F(":"));
    if (gps.time.second() < 10) Serial.print(F("0"));
    Serial.print(gps.time.second());
    Serial.print(F("."));
    if (gps.time.centisecond() < 10) Serial.print(F("0"));
    Serial.print(gps.time.centisecond());
  }
  else
  {
    Serial.print(F("INVALID"));
  }

  Serial.println();
}

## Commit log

2017-12-31 Created folders
2017-12-31 added user manual
2017-12-31 updated user manual
2017-12-31 updated readme and user manual
2018-07-05 readme update
